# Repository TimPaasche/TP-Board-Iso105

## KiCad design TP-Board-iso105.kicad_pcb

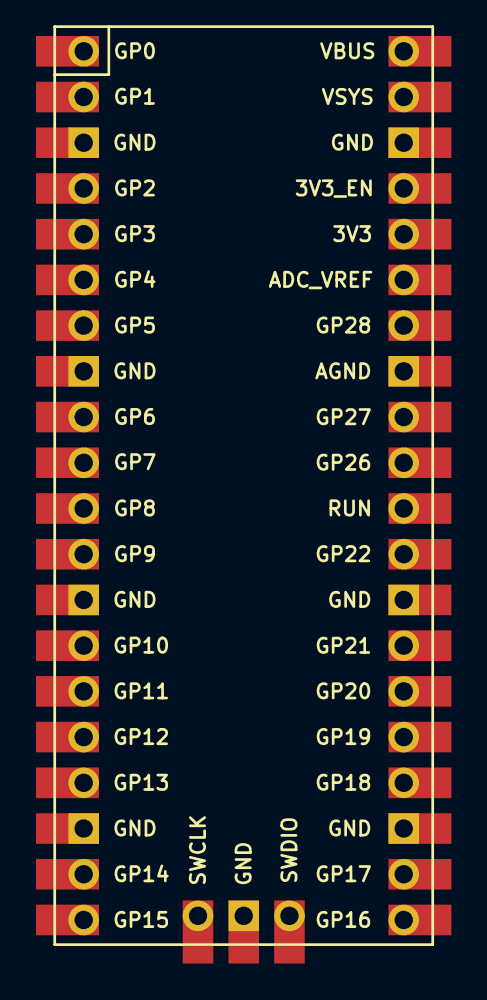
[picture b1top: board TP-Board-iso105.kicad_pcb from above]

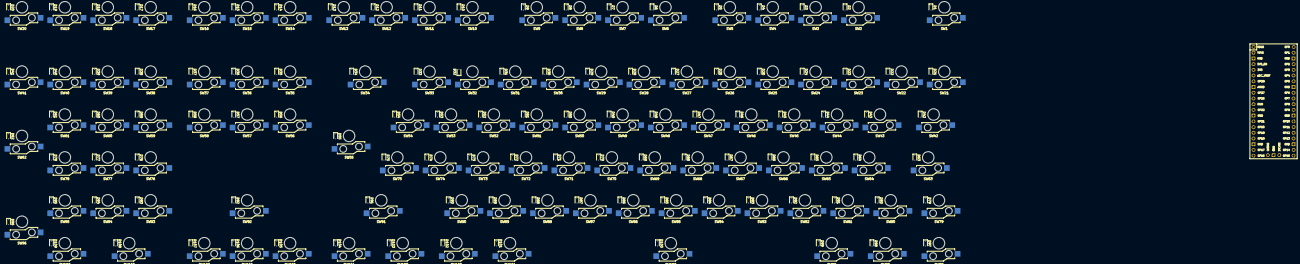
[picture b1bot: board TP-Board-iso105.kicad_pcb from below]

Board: 2 copper layers, 219 parts (109 on the bottom side), 134 nets, no tracks yet.

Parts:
D1, D2, D3, D4, D5, D6, D7, D8, D9, D10, D11, D12, D13, D14, D15, D16, D17, D18, D19, D20, D21, D22, D23, D24, D25, D26, D27, D28, D29, D30, D31, D32, D33, D34, D35, D36, D37, D38, D39, D40, D41, D42, D43, D44, D45, D46, D47, D48, D49, D50, D51, D52, D53, D54, D55, D56, D57, D58, D59, D60, D61, D62, D63, D64, D65, D66, D67, D68, D69, D70, D71, D72, D73, D74, D75, D76, D77, D78, D79, D80, D81, D82, D83, D84, D85, D86, D87, D88, D89, D90, D91, D92, D93, D94, D95, D96, D97, D98, D99, D100, D101, D102, D103, D104, D105, D106, D107, D108, D109: 1N4148; D_SOD-323F
SW1, SW2, SW3, SW4, SW5, SW6, SW7, SW8, SW9, SW10, SW11, SW12, SW13, SW14, SW15, SW16, SW17, SW18, SW19, SW20, SW21, SW22, SW23, SW24, SW25, SW26, SW27, SW28, SW29, SW30, SW31, SW32, SW33, SW34, SW35, SW36, SW37, SW38, SW39, SW40, SW41, SW42, SW43, SW44, SW45, SW46, SW47, SW48, SW49, SW50, SW51, SW52, SW53, SW54, SW55, SW56, SW57, SW58, SW59, SW60, SW61, SW62, SW63, SW64, SW65, SW66, SW67, SW68, SW69, SW70, SW71, SW72, SW73, SW74, SW75, SW76, SW77, SW78, SW79, SW80, SW81, SW82, SW83, SW84, SW85, SW86, SW87, SW88, SW89, SW90, SW91, SW92, SW93, SW94, SW95, SW96, SW97, SW98, SW99, SW100, SW101, SW102, SW103, SW104, SW105, SW106, SW107, SW108, SW109: SW_Push; Gateron_Low_Profile_Socket
U1: Raspberry_Pi_Pico

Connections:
COL0: SW1.1, SW17.1, SW21.1, SW42.1, SW63.1, SW79.1, SW93.1, SW97.1, U1.11 (GPIO8)
COL1: SW18.1, SW22.1, SW43.1, SW64.1, SW80.1, SW94.1, SW98.1, U1.12 (GPIO9)
COL2: SW2.1, SW19.1, SW23.1, SW44.1, SW65.1, SW81.1, SW95.1, SW99.1, U1.14 (GPIO10)
COL3: SW3.1, SW20.1, SW24.1, SW45.1, SW66.1, SW82.1, SW96.1, U1.15 (GPIO11)
COL4: SW4.1, SW25.1, SW38.1, SW46.1, SW67.1, SW83.1, SW108.1, U1.16 (GPIO12)
COL5: SW5.1, SW26.1, SW39.1, SW47.1, SW68.1, SW84.1, SW109.1, U1.17 (GPIO13)
COL6: SW6.1, SW27.1, SW40.1, SW48.1, SW69.1, SW85.1, SW100.1, U1.19 (GPIO14)
COL7: SW7.1, SW28.1, SW41.1, SW49.1, SW70.1, SW86.1, U1.20 (GPIO15)
COL8: SW8.1, SW29.1, SW50.1, SW59.1, SW71.1, SW87.1, U1.21 (GPIO16)
COL9: SW9.1, SW30.1, SW51.1, SW60.1, SW72.1, SW88.1, U1.22 (GPIO17)
COL10: SW10.1, SW31.1, SW52.1, SW61.1, SW73.1, SW89.1, SW101.1, U1.24 (GPIO18)
COL11: SW11.1, SW32.1, SW53.1, SW62.1, SW74.1, SW90.1, SW102.1, U1.25 (GPIO19)
COL12: SW12.1, SW33.1, SW54.1, SW75.1, SW76.1, SW103.1, U1.26 (GPIO20)
COL13: SW13.1, SW34.1, SW55.1, SW77.1, SW91.1, SW104.1, U1.27 (GPIO21)
COL14: SW14.1, SW35.1, SW56.1, SW78.1, SW105.1, U1.29 (GPIO22)
COL15: SW15.1, SW36.1, SW57.1, SW92.1, SW106.1, U1.31 (GPIO26_ADC0)
COL16: SW16.1, SW37.1, SW58.1, SW107.1, U1.32 (GPIO27_ADC1)
unnamed: D1.2 (A), SW1.2
unnamed: D2.2 (A), SW2.2
unnamed: D3.2 (A), SW3.2
unnamed: D4.2 (A), SW4.2
unnamed: D5.2 (A), SW5.2
unnamed: D6.2 (A), SW6.2
unnamed: D7.2 (A), SW7.2
unnamed: D8.2 (A), SW8.2
unnamed: D9.2 (A), SW9.2
unnamed: D10.2 (A), SW10.2
unnamed: D11.2 (A), SW11.2
unnamed: D12.2 (A), SW12.2
unnamed: D13.2 (A), SW13.2
unnamed: D14.2 (A), SW14.2
unnamed: D15.2 (A), SW15.2
unnamed: D16.2 (A), SW16.2
unnamed: D17.2 (A), SW17.2
unnamed: D18.2 (A), SW18.2
unnamed: D19.2 (A), SW19.2
unnamed: D20.2 (A), SW20.2
unnamed: D21.2 (A), SW21.2
unnamed: D22.2 (A), SW22.2
unnamed: D23.2 (A), SW23.2
unnamed: D24.2 (A), SW24.2
unnamed: D25.2 (A), SW25.2
unnamed: D26.2 (A), SW26.2
unnamed: D27.2 (A), SW27.2
unnamed: D28.2 (A), SW28.2
unnamed: D29.2 (A), SW29.2
unnamed: D30.2 (A), SW30.2
unnamed: D31.2 (A), SW31.2
unnamed: D32.2 (A), SW32.2
unnamed: D33.2 (A), SW33.2
unnamed: D34.2 (A), SW34.2
unnamed: D35.2 (A), SW35.2
unnamed: D36.2 (A), SW36.2
unnamed: D37.2 (A), SW37.2
unnamed: D38.2 (A), SW38.2
unnamed: D39.2 (A), SW39.2
unnamed: D40.2 (A), SW40.2
unnamed: D41.2 (A), SW41.2
unnamed: D42.2 (A), SW42.2
unnamed: D43.2 (A), SW43.2
unnamed: D44.2 (A), SW44.2
unnamed: D45.2 (A), SW45.2
unnamed: D46.2 (A), SW46.2
unnamed: D47.2 (A), SW47.2
unnamed: D48.2 (A), SW48.2
unnamed: D49.2 (A), SW49.2
unnamed: D50.2 (A), SW50.2
unnamed: D51.2 (A), SW51.2
unnamed: D52.2 (A), SW52.2
unnamed: D53.2 (A), SW53.2
unnamed: D54.2 (A), SW54.2
unnamed: D55.2 (A), SW55.2
unnamed: D56.2 (A), SW56.2
unnamed: D57.2 (A), SW57.2
unnamed: D58.2 (A), SW58.2
unnamed: D59.2 (A), SW59.2
unnamed: D60.2 (A), SW60.2
unnamed: D61.2 (A), SW61.2
unnamed: D62.2 (A), SW62.2
unnamed: D63.2 (A), SW63.2
unnamed: D64.2 (A), SW64.2
unnamed: D65.2 (A), SW65.2
unnamed: D66.2 (A), SW66.2
unnamed: D67.2 (A), SW67.2
unnamed: D68.2 (A), SW68.2
unnamed: D69.2 (A), SW69.2
unnamed: D70.2 (A), SW70.2
unnamed: D71.2 (A), SW71.2
unnamed: D72.2 (A), SW72.2
unnamed: D73.2 (A), SW73.2
unnamed: D74.2 (A), SW74.2
unnamed: D75.2 (A), SW75.2
unnamed: D76.2 (A), SW76.2
unnamed: D77.2 (A), SW77.2
unnamed: D78.2 (A), SW78.2
unnamed: D79.2 (A), SW79.2
unnamed: D80.2 (A), SW80.2
unnamed: D81.2 (A), SW81.2
unnamed: D82.2 (A), SW82.2
unnamed: D83.2 (A), SW83.2
unnamed: D84.2 (A), SW84.2
unnamed: D85.2 (A), SW85.2
unnamed: D86.2 (A), SW86.2
unnamed: D87.2 (A), SW87.2
unnamed: D88.2 (A), SW88.2
unnamed: D89.2 (A), SW89.2
unnamed: D90.2 (A), SW90.2
unnamed: D91.2 (A), SW91.2
unnamed: D92.2 (A), SW92.2
unnamed: D93.2 (A), SW93.2
unnamed: D94.2 (A), SW94.2
unnamed: D95.2 (A), SW95.2
unnamed: D96.2 (A), SW96.2
unnamed: D97.2 (A), SW97.2
unnamed: D98.2 (A), SW98.2
unnamed: D99.2 (A), SW99.2
unnamed: D100.2 (A), SW100.2
unnamed: D101.2 (A), SW101.2
unnamed: D102.2 (A), SW102.2
unnamed: D103.2 (A), SW103.2
unnamed: D104.2 (A), SW104.2
unnamed: D105.2 (A), SW105.2
unnamed: D106.2 (A), SW106.2
unnamed: D107.2 (A), SW107.2
unnamed: D108.2 (A), SW108.2
unnamed: D109.2 (A), SW109.2
ROW0: D1.1 (K), D2.1 (K), D3.1 (K), D4.1 (K), D5.1 (K), D6.1 (K), D7.1 (K), D8.1 (K), D9.1 (K), D10.1 (K), D11.1 (K), D12.1 (K), D13.1 (K), D14.1 (K), D15.1 (K), D16.1 (K), U1.1 (GPIO0)
ROW1: D21.1 (K), D22.1 (K), D23.1 (K), D24.1 (K), D25.1 (K), D26.1 (K), D27.1 (K), D28.1 (K), D29.1 (K), D30.1 (K), D31.1 (K), D32.1 (K), D33.1 (K), D34.1 (K), D35.1 (K), D36.1 (K), D37.1 (K), U1.2 (GPIO1)
ROW2: D42.1 (K), D43.1 (K), D44.1 (K), D45.1 (K), D46.1 (K), D47.1 (K), D48.1 (K), D49.1 (K), D50.1 (K), D51.1 (K), D52.1 (K), D53.1 (K), D54.1 (K), D55.1 (K), D56.1 (K), D57.1 (K), D58.1 (K), U1.4 (GPIO2)
ROW3: D63.1 (K), D64.1 (K), D65.1 (K), D66.1 (K), D67.1 (K), D68.1 (K), D69.1 (K), D70.1 (K), D71.1 (K), D72.1 (K), D73.1 (K), D74.1 (K), D75.1 (K), U1.5 (GPIO3)
ROW4: D79.1 (K), D80.1 (K), D81.1 (K), D82.1 (K), D83.1 (K), D84.1 (K), D85.1 (K), D86.1 (K), D87.1 (K), D88.1 (K), D89.1 (K), D90.1 (K), D91.1 (K), D92.1 (K), U1.6 (GPIO4)
ROW5: D97.1 (K), D98.1 (K), D99.1 (K), D100.1 (K), D101.1 (K), D102.1 (K), D103.1 (K), D104.1 (K), D105.1 (K), D106.1 (K), D107.1 (K), U1.7 (GPIO5)
ROW6: D17.1 (K), D18.1 (K), D19.1 (K), D20.1 (K), D38.1 (K), D39.1 (K), D40.1 (K), D41.1 (K), D59.1 (K), D60.1 (K), D61.1 (K), D62.1 (K), D76.1 (K), D77.1 (K), D78.1 (K), U1.8 (GND)
ROW7: D93.1 (K), D94.1 (K), D95.1 (K), D96.1 (K), D108.1 (K), D109.1 (K), U1.9 (GPIO6)
